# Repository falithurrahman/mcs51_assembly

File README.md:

### Description

#### 1. Minimum_System_MCS1
I made the minimum system of MCS51 microcontroller at this project. You can find the example of MC51's minimum system schematic on the internet, there's a lot of it. But at this project i use my creativity to route and wire the minimum system board on my own. The components needed for this project included :
1. AT89S51 IC
2. LM7805 regulator
3. Crystal 22 MHz
4. 2x Capacitor 22pF
5. LED
6. Pushbuttons
7. Pinheaders
8. DC female jack

You can take a look at the picture below for the example schematic. I got this picture available online from [here](https://www.inzarsalfikar.com/2011/03/minimum-system-at89s51-at89s52-skematic.html). But for this project i made some modification for the schematic that you can see at the PCB folder.

You can upload program to this board using USBASP programmer which can be purchased at local electronic stores. I've also created the port to upload program by extending the MOSI, MISO, and SCK pin. To test whether this board working or not, i upload a simple program to blink the LED in port 0. The file is main.asm that available in this repository.

#### 2. Water_level Sensor

I made the detector of water level using MCS51 as the microcontroller. I used 2 sensors for this project, one at the bottom of the tank and another one at the top of the tank. You can see the clear picture below   

Sensor i used in this project is very simple. I made two nearly-connected conductor surface at dot matrix PCB. Each of this surface was extended with cable and connected to my comparator board. The design of this board is available at PCB folder of water_level_sensor project. 
Then the sensor was connected to comparator, i used LM324 as the comparator.

The idea is quite simple. If there is no water touches the sensor, the resistance of the sensor is very high because it's open circuit. Because of this resistance value, the comparator will generate low logic. And vice versa, the comparator will generate high logic if there is water touches the sensor. The comparator board is equipped with LED as an indicator.

#### 3. Servo

I move a servo using MCS51 with assembly language in this project. It may look simple, but generating pulse with this primitive language is not as easy as it said. The type of servo i used is tower pro sg90. This servo works between 0-2ms with period of 20ms. 

By setting the pulse 1.5ms, the servo moves to position "0". Pulse 1ms sets the servo to position "90" and pulse 2 sets the servo to position "-90".

#### 4. Pulse_read

This project include arduino nano as a pulse generator. Arduino nano will generate pulse with a frequency that depends on analog read value from potentiometer. This pulse will be read by the mcs51 board that connected to the LCD. This LCD then display the value of pulse. The code for mcs51 board is available in the assembly code folder and arduino code is available in arduino code folder of pulse_read project. The LCD type used in this project is Dot Matrix Liquid Crystal Display (LCD) HD44780.

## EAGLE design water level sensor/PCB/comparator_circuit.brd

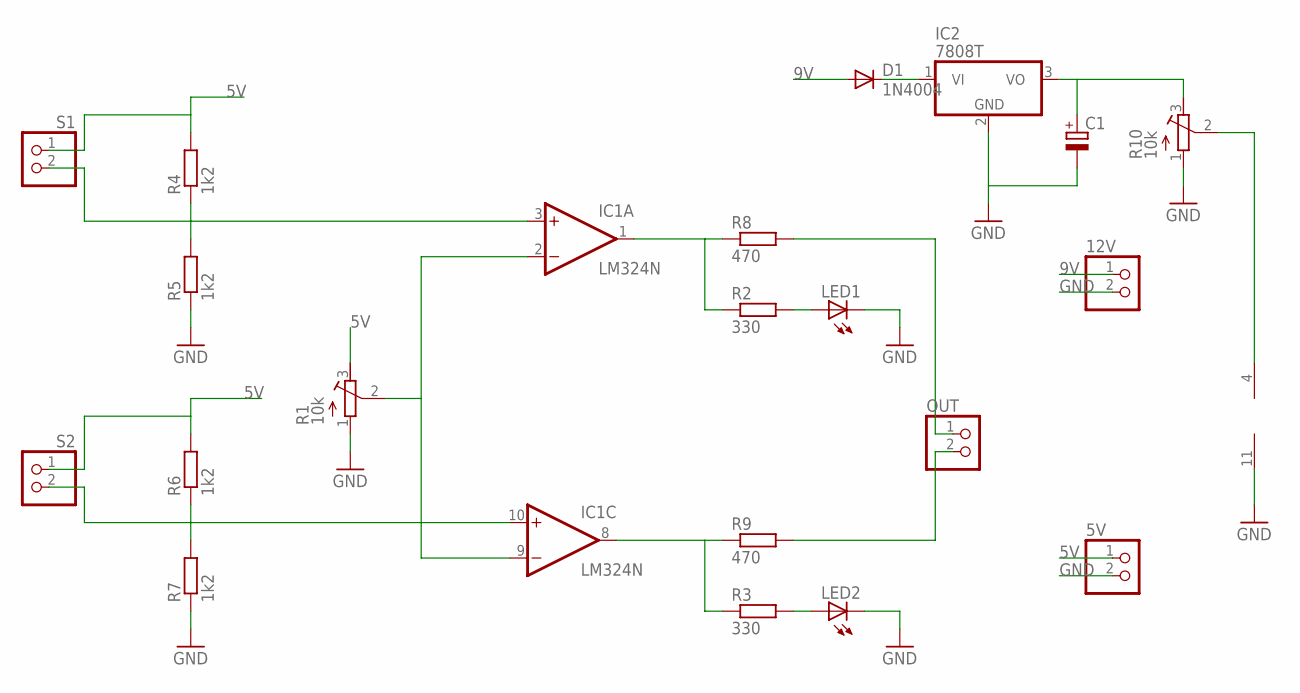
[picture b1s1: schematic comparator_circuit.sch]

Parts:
5V, 12V: PINHD-1X2; 1X02
C1: CPOL-EUE2.5-6; E2,5-6
D1: 1N4004; DO41-10
IC1: LM324N; DIL14
IC2: 7808T; TO220H
LED1, LED2: LED3MM
OUT: PINHD-1X2; 1X02
R1, R10: 10k; RTRIM3339P
R2, R3: 330; 0204/7
R4, R5, R6, R7: 1k2; 0204/7
R8, R9: 470; 0204/7
S1, S2: PINHD-1X2; 1X02

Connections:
5V: 5V.1, R1.3 (E), R4.2, R6.2, S1.1, S2.1
9V: 12V.1, D1.A
GND: 5V.2, 12V.2, C1.-, IC1.11 (V-), IC2.2 (GND), LED1.K (C), LED2.K (C), R1.1 (A), R5.1, R7.1, R10.1 (A)
unnamed: IC1.2 (-IN), IC1.9 (-IN), R1.2 (S)
unnamed: D1.C, IC2.1 (VI)
unnamed: LED1.A, R2.2
unnamed: LED2.A, R3.2
unnamed: IC1.8 (OUT), R3.1, R9.1
unnamed: IC1.3 (+IN), R4.1, R5.2, S1.2
unnamed: IC1.10 (+IN), R6.1, R7.2, S2.2
unnamed: C1.+, IC2.3 (VO), R10.3 (E)
unnamed: IC1.4 (V+), R10.2 (S)
unnamed: OUT.1, R8.2
unnamed: OUT.2, R9.2
unnamed: IC1.1 (OUT), R2.1, R8.1

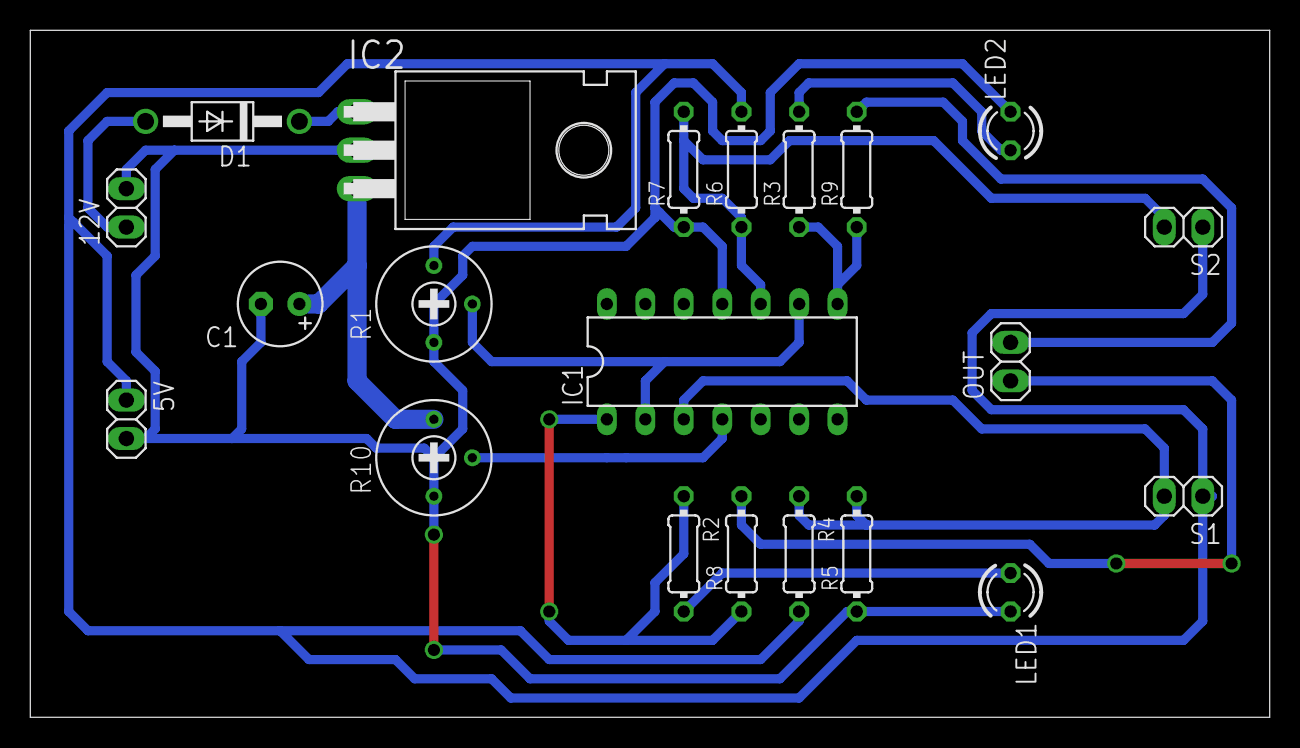
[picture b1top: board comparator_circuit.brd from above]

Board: 2 copper layers, 81.9 x 45.4 mm, 21 parts (0 on the bottom side), 15 nets.

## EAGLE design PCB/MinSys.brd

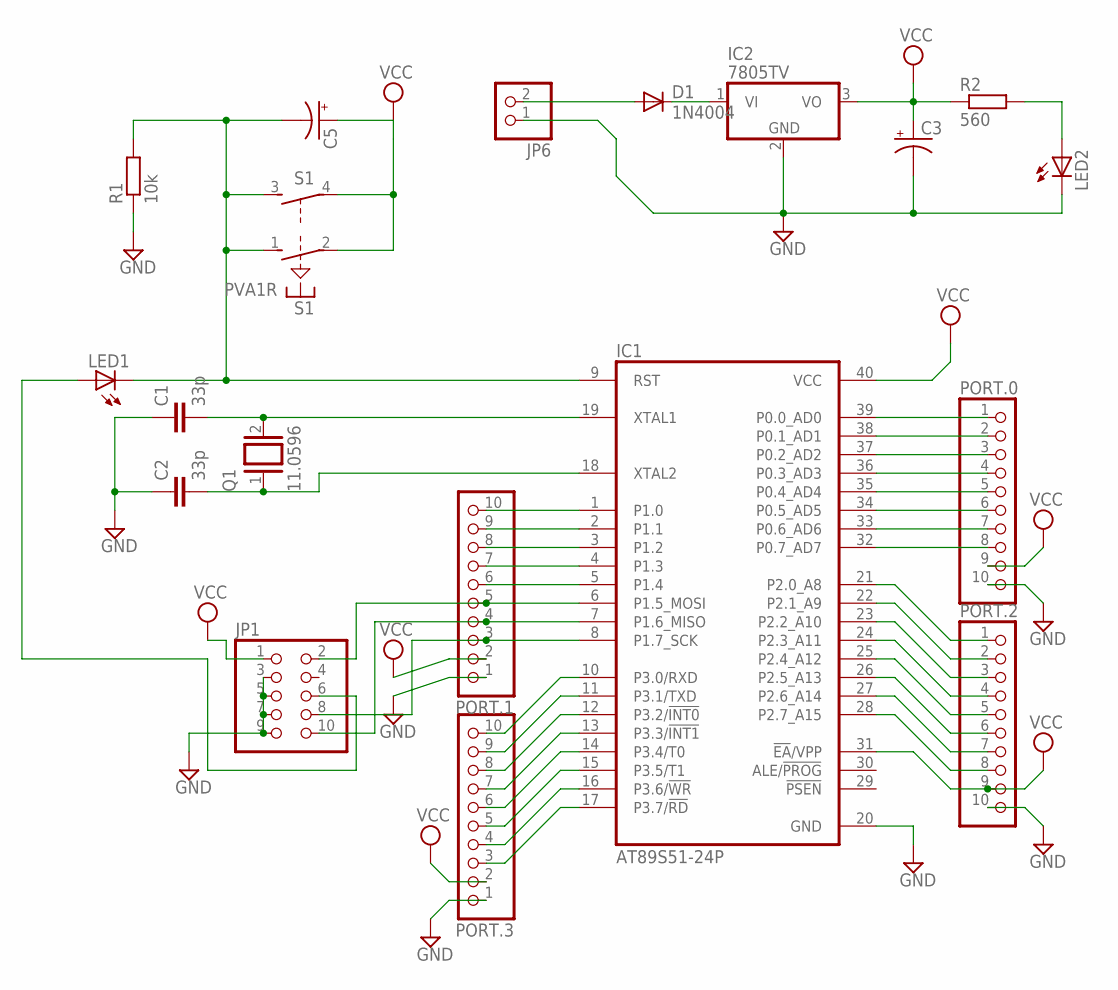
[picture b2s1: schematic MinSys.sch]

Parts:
C1, C2: 33p; C2.5-3
C3: CPOL-USE3.5-8; E3,5-8
C5: CPOL-USE2.5-6; E2,5-6
D1: 1N4004; DO41-10
IC1: AT89S51-24P; DIL40
IC2: 7805TV; TO220V
JP1: PINHD-2X5; 2X05
JP6: PINHD-1X2; 1X02
LED1, LED2: LED3MM
PORT.0, PORT.1, PORT.2, PORT.3: PINHD-1X10; 1X10
Q1: 11.0596; QS
R1: 10k; 0207/10
R2: 560; 0207/10
S1: PVA1R

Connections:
GND: C1.1, C2.1, C3.-, IC1.20 (GND), IC2.2 (GND), JP1.3, JP1.5, JP1.7, JP1.9, JP6.1, LED2.K (C), PORT.0.10, PORT.1.1, PORT.2.10, PORT.3.1, R1.1
unnamed: IC1.10 (P3.0/RXD), PORT.3.10
unnamed: IC1.11 (P3.1/TXD), PORT.3.9
unnamed: IC1.12 (P3.2/!INT0), PORT.3.8
unnamed: IC1.13 (P3.3/!INT1), PORT.3.7
unnamed: IC1.14 (P3.4/T0), PORT.3.6
unnamed: IC1.15 (P3.5/T1), PORT.3.5
unnamed: IC1.16 (P3.6/!WR), PORT.3.4
unnamed: IC1.17 (P3.7/!RD), PORT.3.3
unnamed: C1.2, IC1.19 (XTAL1), Q1.2
unnamed: C2.2, IC1.18 (XTAL2), Q1.1
unnamed: IC1.21 (P2.0_A8), PORT.2.1
unnamed: IC1.22 (P2.1_A9), PORT.2.2
unnamed: IC1.23 (P2.2_A10), PORT.2.3
unnamed: IC1.24 (P2.3_A11), PORT.2.4
unnamed: IC1.25 (P2.4_A12), PORT.2.5
unnamed: IC1.26 (P2.5_A13), PORT.2.6
unnamed: IC1.27 (P2.6_A14), PORT.2.7
unnamed: IC1.28 (P2.7_A15), PORT.2.8
unnamed: IC1.1 (P1.0), PORT.1.10
unnamed: IC1.2 (P1.1), PORT.1.9
unnamed: IC1.3 (P1.2), PORT.1.8
unnamed: IC1.4 (P1.3), PORT.1.7
unnamed: IC1.5 (P1.4), PORT.1.6
unnamed: D1.A, JP6.2
unnamed: IC1.7 (P1.6_MISO), JP1.10, PORT.1.4
unnamed: IC1.8 (P1.7_SCK), JP1.8, PORT.1.3
unnamed: IC1.39 (P0.0_AD0), PORT.0.1
unnamed: IC1.38 (P0.1_AD1), PORT.0.2
unnamed: IC1.37 (P0.2_AD2), PORT.0.3
unnamed: IC1.36 (P0.3_AD3), PORT.0.4
unnamed: IC1.35 (P0.4_AD4), PORT.0.5
unnamed: IC1.34 (P0.5_AD5), PORT.0.6
unnamed: IC1.33 (P0.6_AD6), PORT.0.7
unnamed: IC1.32 (P0.7_AD7), PORT.0.8
unnamed: JP1.6, LED1.A
unnamed: D1.C, IC2.1 (VI)
unnamed: C5.-, IC1.9 (RST), LED1.K (C), R1.2, S1.1 (S), S1.3 (S)
unnamed: IC1.6 (P1.5_MOSI), JP1.2, PORT.1.5
unnamed: LED2.A, R2.2
VCC: C3.+, C5.+, IC1.31 (!EA!/VPP), IC1.40 (VCC), IC2.3 (VO), JP1.1, PORT.0.9, PORT.1.2, PORT.2.9, PORT.3.2, R2.1, S1.2, S1.4

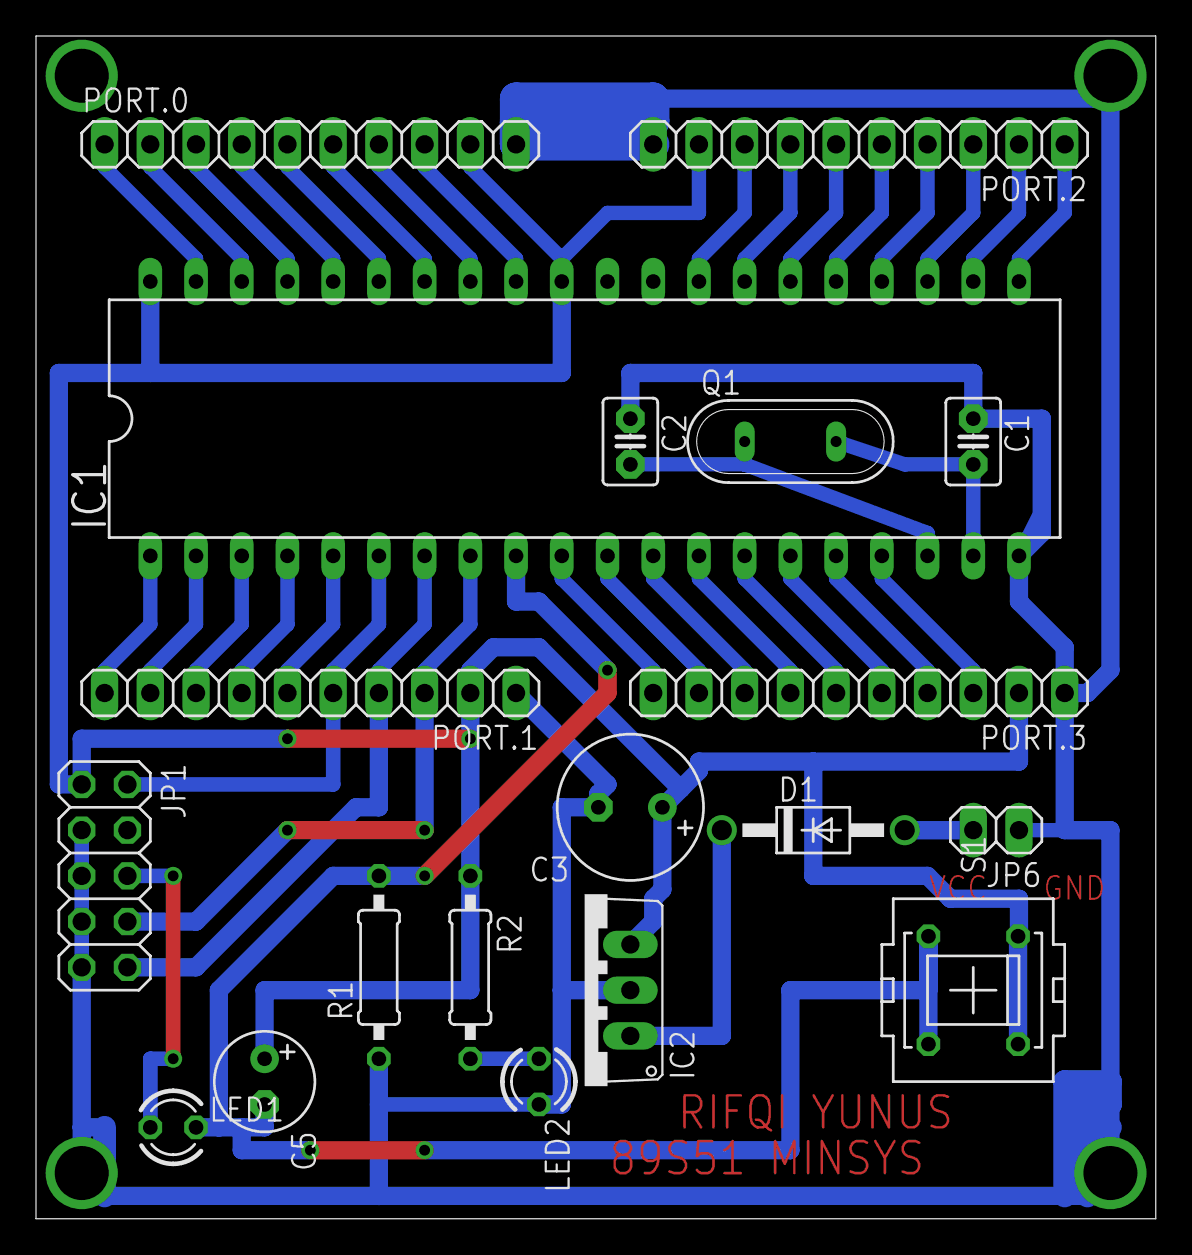
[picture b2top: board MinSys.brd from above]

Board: 2 copper layers, 62.2 x 65.7 mm, 19 parts (0 on the bottom side), 41 nets.

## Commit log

2019-10-01 add picture and edit readme
2019-10-01 edited readme
2019-10-01 moved to new folder
2019-10-01 added new water_level_sensor
2019-10-01 added new servo
2019-10-01 add new pulse_read
2019-10-02 add new water_level_sensor desc
2019-10-02 add new picture and edit readme
2019-10-02 add new lcd folder and edit readme
2019-10-02 edit readme
